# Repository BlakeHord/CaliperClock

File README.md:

# Caliper Clock

A low-power digital clock that uses the LCD salvaged from a cheap digital
caliper. The custom board drops into the caliper body, drives its 4-mux glass
directly, and is designed to operate for >1 year off a single 1.5V LR44 button cell.

Three major hardware revisions live in this repo.

## Revisions

| Dir | Board | Status |
|-----|-------|--------|
| [`Caliper_Clock_V1/`](Caliper_Clock_V1/) | ATtiny1616 + HT1621B LCD driver + RV-3028 RTC (incl. a test board) | original design |
| [`Caliper_Clock_V2/`](Caliper_Clock_V2/) | revised V1-class board **+ the working V2 firmware** | source of truth for the caliper LCD segment map & set-time UX. Battery depleted in days due to constant boost switching (wrong component choice) |
| [`Caliper_Clock_V3/`](Caliper_Clock_V3/) | **active redesign** around an **MSP430FR4133** (FRAM, integrated LCD_E + RTC, no HT1621) | hardware-verified, firmware **v1.0** running on the custom board |

**Active work is V3.** Its firmware ports the V2 segment map and time-setting
state machine onto the MSP430, displaying time on the real caliper glass via the
chip's built-in LCD controller and keeping time with the integrated RTC.

## V3 at a glance

- **MCU:** MSP430FR4133 (LCD_E drives the 4-mux caliper glass directly).
- **Power:** boosts a 1.5 V LR44 cell to 3.0 V (TPS61099); sleeps in LPM3 with
  the always-on LCD, targeting ~µA average for >year battery life.
- **Firmware:** `Caliper_Clock_V3/firmware/` — MSP430-GCC + `mspdebug`. The
  default build is the v1.0 product (full clock + buttons on the caliper glass);
  numbered diagnostic builds remain for bring-up. See its
  [README](Caliper_Clock_V3/firmware/README.md).
- **Hardware:** KiCad design, datasheets, and gerbers under `Caliper_Clock_V3/`.

```sh
cd Caliper_Clock_V3/firmware
make            # build v1.0 (the product)
make flash      # build + flash via the LaunchPad's eZ-FET (Spy-Bi-Wire)
```

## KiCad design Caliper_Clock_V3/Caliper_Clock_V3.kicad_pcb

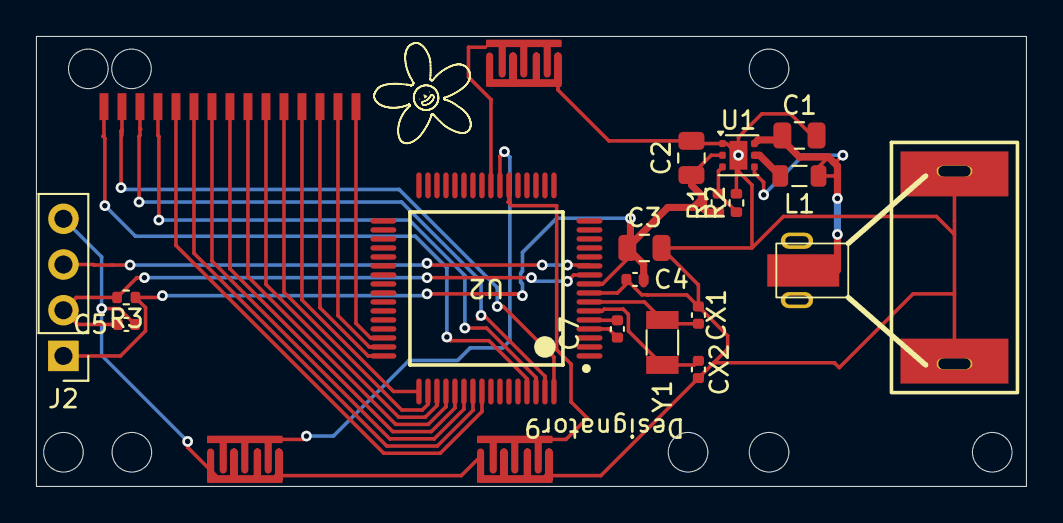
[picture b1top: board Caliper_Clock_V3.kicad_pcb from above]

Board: 2 copper layers, 55.0 x 25.0 mm, 22 parts (0 on the bottom side), 29 nets.

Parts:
C1, C2, C3: 10uF; C_0805_2012Metric
C4, C7: 100nF; C_0402_1005Metric
C5: 1nF; C_0402_1005Metric
CL_1: MY-ZJ-117
CL_2: MY-ZJ-118
CX1, CX2: 12pF; C_0402_1005Metric
J1: LCD PADS
J2: SBW; PinHeader_1x04_P2.54mm_Vertical
L1: 2.2uH; L_0805_2012Metric
R1: 2.0M; R_0402_1005Metric
R2: 1.0M; R_0402_1005Metric
R3: 47k; R_0402_1005Metric
SW1: MODE; Button_trace_caliper_board
SW2: HOUR; Button_trace_caliper_board
SW3: MIN; Button_trace_caliper_board
U1: TPS61099DRVR; WSON-6-1EP_2x2mm_P0.65mm_EP1x1.6mm
U2: MSP430FR4133IPM; PM0064A_N
Y1: 32.768kHz; Crystal_SMD_3215-2Pin_3.2x1.5mm

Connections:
+3V0: C2.1, C3.1, C4.1, J2.1, R1.1, R3.1, U1.2 (VOUT), U2.9 (DVCC)
+BATT: C1.1, L1.1, U1.4 (EN), U1.6 (VIN)
/BTN_HOUR: SW2.1, U2.23 (P1.1_UCA0RXD_UCA0SOMI_A1_Veref+)
/BTN_MIN: SW3.1, U2.22 (P1.2_UCA0CLK_A2)
/BTN_MODE: SW1.1, U2.24 (P1.0_UCA0TXD_UCA0SIMO_A0_Veref-)
/LCD_COM0: J1.2, U2.64 (P7.0_L0)
/LCD_COM1: J1.3, U2.63 (P7.1_L1)
/LCD_COM2: J1.4, U2.62 (P7.2_L2)
/LCD_COM3: J1.1, U2.61 (P7.3_L3)
/LCD_SEG0: J1.5, U2.56 (P3.0_L8)
/LCD_SEG1: J1.6, U2.55 (P3.1_L9)
/LCD_SEG2: J1.7, U2.54 (P3.2_L10)
/LCD_SEG3: J1.8, U2.53 (P3.3_L11)
/LCD_SEG4: J1.9, U2.52 (P3.4_L12)
/LCD_SEG5: J1.10, U2.51 (P3.5_L13)
/LCD_SEG6: J1.11, U2.50 (P3.6_L14)
/LCD_SEG7: J1.12, U2.49 (P3.7_L15)
/LCD_SEG8: J1.13, U2.48 (P6.0_L16)
/LCD_SEG9: J1.14, U2.47 (P6.1_L17)
/LCD_SEG10: J1.15, U2.46 (P6.2_L18)
/RST_n: C5.1, J2.2, R3.2, U2.10 (RST_NMI_SBWTDIO_N)
/TEST_SBWTCK: J2.3, U2.11 (TEST_SBWTCK)
/XIN: CX1.1, U2.7 (P4.1_XIN), Y1.1
/XOUT: CX2.1, U2.6 (P4.2_XOUT), Y1.2
GND: C1.2, C2.2, C3.2, C4.2, C5.2, CX1.2, CX2.2, J2.4, R2.2, SW1.2, SW2.2, SW3.2, U1.1 (GND), U1.7 (PAD/GND), U2.8 (DVSS)
unnamed: R1.2, R2.1, U1.3 (FB)
unnamed: L1.2, U1.5 (SW)
unnamed: C7.2, U2.5 (P4.3_LCDCAP0)
unnamed: C7.1, U2.4 (P4.4_LCDCAP1)

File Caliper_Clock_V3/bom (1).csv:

Comment,Designator,Footprint,LCSC Part #
"10uF","C1,C2,C3","C_0805_2012Metric","C15850"
"100nF","C4,C7","C_0402_1005Metric","C1525"
"1nF","C5","C_0402_1005Metric","C1523"
"12pF","CX1,CX2","C_0402_1005Metric","C1547"
"2.0M","R1","R_0402_1005Metric","C11512"
"1.0M","R2","R_0402_1005Metric","C26083"
"47k","R3","R_0402_1005Metric","C25792"
"2.2uH","L1","L_0805_2012Metric","C41651"
"32.768kHz","Y1","Crystal_SMD_3215-2Pin_3.2x1.5mm","C32346"
"TPS61099DRVR","U1","WSON-6-1EP_2x2mm_P0.65mm_EP1x1.6mm","C2842395"
"MSP430FR4133IPM","U2","PM0064A_N","C106759"
"MY-ZJ-117","CL_1","MY-ZJ-117","C964865"
"MY-FJ-118","CL_2","MY-FJ-118","C964866"

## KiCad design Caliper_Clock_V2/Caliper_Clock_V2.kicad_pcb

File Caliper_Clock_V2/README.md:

# Caliper Clock

A low-power digital clock built using a salvaged LCD display from a digital caliper, driven by an ATtiny1616 microcontroller with an RV-3028 real-time clock.

## Features

- **Ultra-low power consumption** — ATtiny1616 sleeps in power-down mode, waking only on RTC minute interrupts
- **12-hour time display** with AM/PM indicator and blinking colon
- **Button-based time setting** — long-press to enter setting mode, adjust hours/minutes with dedicated buttons
- **Accurate timekeeping** — RV-3028 RTC with minute-update interrupt
- **Repurposed LCD** — uses an HT1621B-compatible LCD from a digital caliper (4-digit 7-segment display)

## Hardware

### Components

| Component | Description |
|-----------|-------------|
| ATtiny1616 | 8-bit AVR microcontroller, 20 MHz, 20 pins, supports sleep modes, GPIO, interrupts |
| HT1621B | 32-nibble LCD driver, 4-com 1/3-bias, SPI/parallel interface |
| RV-3028 | I2C RTC, 24-hour mode, minute alarm output, ultra-low-power |
| AP3015AKTR-G1 | Boost Switching Regulator IC |

### Pin Mapping

#### LCD (HT1621B)
| Signal | Pin |
|--------|-----|
| DATA   | PA1 |
| WR     | PA7 |
| /CS    | PB3 |

#### RTC (RV-3028 via Soft I²C)
| Signal | Pin |
|--------|-----|
| SDA    | PA2 |
| SCL    | PA3 |
| INT    | PA4 |

#### Buttons
| Function | Pin |
|----------|-----|
| Mode     | PB0 |
| Hour+    | PB1 |
| Minute+  | PB2 |

#### Debug
| Function | Pin |
|----------|-----|
| LED      | PA6 |

## PCB Designs

The repository is organized into one folder per board revision:

- **Caliper_Clock_V1/** — Original board (includes the `Caliper_Clock_Test_Board/` test/development board)
- **Caliper_Clock_V2/** — Revised board design (also contains this firmware and tooling)
- **Caliper_Clock_V3/** — MSP430FR4133-based redesign (includes the `MSP430FR4133IPM/` symbol library)

Each folder contains:
- KiCad schematic (`.kicad_sch`)
- KiCad PCB layout (`.kicad_pcb`)
- Gerber files for manufacturing
- BOM and pick-and-place files

## Building the Firmware

### Prerequisites

- AVR-GCC toolchain (avr-gcc 14 recommended)
- avr-objcopy

On macOS with Homebrew:
```bash
brew install avr-gcc@14
```

### Compile

```bash
make clean
make
```

This produces `blink.hex` ready for flashing.

### Flash

Use a UPDI programmer (e.g., SerialUPDI, Atmel-ICE, or jtag2updi):

```bash
# Example with pymcuprog
pymcuprog write -t uart -u /dev/tty.usbserial-XXXX -d attiny1616 -f blink.hex
```

## Usage

### Normal Operation

- The clock displays time in 12-hour format with AM/PM indicator
- Colon blinks at ~1 Hz
- MCU sleeps between updates for minimal power consumption

### Setting the Time

1. **Long-press the Mode button (PB0)** for ~5 seconds to enter time-setting mode
2. Display will flash to indicate setting mode
3. **Press Hour button (PB1)** to increment hours (1-12)
4. **Press Minute button (PB2)** to increment minutes (0-59)
5. **Press Mode button (PB0)** again to save and exit

Hold Hour or Minute buttons for auto-repeat.

## Firmware Variants

The repository includes several firmware versions:

| File | Description |
|------|-------------|
| `main.c` | Current version with low-power mode and button time-setting |
| `main-CLOCK-V1.c` | Earlier clock implementation |
| `main-BASIC-CLOCK.c` | Basic clock without power optimization |
| `main-RTC-test.c` | RTC testing/debugging |
| `main-lcd_count.c` | LCD counting test |
| `main-lcd_walk.c` | LCD segment walking test |
| `main-blink_WR_CS_LED.c` | GPIO/LED blink test |

## Python Utilities

- **lcd_driver.py** — ESP32 MicroPython LCD driver (for prototyping)
- **lcd_screen_decoding.py** — LCD segment mapping analysis tool

## License

MIT License — feel free to use, modify, and share!

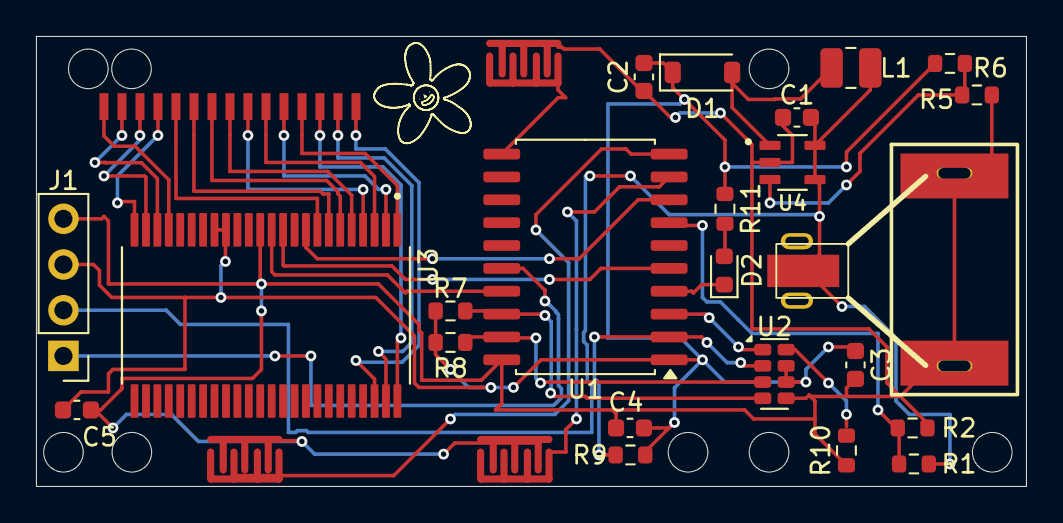
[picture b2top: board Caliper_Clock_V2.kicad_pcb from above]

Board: 2 copper layers, 55.0 x 25.0 mm, 42 parts (0 on the bottom side), 32 nets.

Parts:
C1: 10uF; C_0603_1608Metric
C2: 22uF; C_0603_1608Metric
C3, C4, C5: 0.1uF; C_0603_1608Metric
CL_1: MY-ZJ-117
CL_2: MY-ZJ-118
D1: MBR0540; D_SOD-123
D2: LED; D_0603_1608Metric
J1: Conn_01x04; PinHeader_1x04_P2.54mm_Vertical
L1: 10uH; L_1008_2520Metric
R1: 2.2M; R_0603_1608Metric
R2: 1.0M; R_0603_1608Metric
R5: 1.43M; R_0603_1608Metric
R6: 1.00M; R_0603_1608Metric
R7, R8: 10k; R_0603_1608Metric
R9: 47k; R_0603_1608Metric
R10: 100k; R_0603_1608Metric
R11: 1.1k; R_0603_1608Metric
TP1: PAD1; TestPoint_Pad_0.5mm_x_5.0mm
TP2: PAD2; TestPoint_Pad_0.5mm_x_5.0mm
TP3: PAD3; TestPoint_Pad_0.5mm_x_5.0mm
TP4: PAD4; TestPoint_Pad_0.5mm_x_5.0mm
TP5: PAD5; TestPoint_Pad_0.5mm_x_5.0mm
TP6: PAD6; TestPoint_Pad_0.5mm_x_5.0mm
TP7: PAD7; TestPoint_Pad_0.5mm_x_5.0mm
TP8: PAD8; TestPoint_Pad_0.5mm_x_5.0mm
TP9: PAD9; TestPoint_Pad_0.5mm_x_5.0mm
TP10: PAD10; TestPoint_Pad_0.5mm_x_5.0mm
TP11: PAD11; TestPoint_Pad_0.5mm_x_5.0mm
TP12: PAD12; TestPoint_Pad_0.5mm_x_5.0mm
TP13: PAD13; TestPoint_Pad_0.5mm_x_5.0mm
TP14: PAD14; TestPoint_Pad_0.5mm_x_5.0mm
TP15: PAD15; TestPoint_Pad_0.5mm_x_5.0mm
TP17: BTN2; Button_trace_caliper_board
TP18: BTN3; Button_trace_caliper_board
TP19: BTN4; Button_trace_caliper_board
U1: ATtiny1616-S; SOIC-20W_7.5x12.8mm_P1.27mm
U2: RV-3028-C7; MicroCrystal_C7_SON-8_1.5x3.2mm_P0.9mm
U3: HT1621B; SOP63P1035X279-48N
U4: AP3015AKTR-G1; SOT95P280X145-5N

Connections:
+1V5: C1.1, CL_1.3, J1.2, L1.2, R1.2, U4.4 (~SHDN), U4.5 (VIN)
+3V0: C2.2, C3.1, C4.2, C5.1, D1.1 (K), J1.3, R5.2, R7.2, R8.2, R9.2, R11.1, U1.1 (VCC), U2.6 (VBACKUP), U2.7 (VDD), U3.16 (VLCD), U3.17 (VDD)
/BAT_SENSE: R1.1, R2.2, U1.7 (PB4)
/CLKOUT: U1.3 (PA5), U2.1 (CLKOUT)
/COM0: TP1.1, U3.21 (COM0)
/COM1: TP2.1, U3.22 (COM1)
/COM2: TP3.1, U3.23 (COM2)
/COM3: TP4.1, U3.24 (COM3)
/INT: R9.1, U1.2 (PA4), U2.2 (~INT)
/LCD_CS: U1.8 (PB3), U3.9 (~CS)
/LCD_DATA: U1.17 (PA1), U3.12 (DATA)
/LCD_WR: U1.5 (PA7), U3.11 (~WR)
/SCL: R8.1, U1.19 (PA3), U2.3 (SCL)
/SDA: R7.1, U1.18 (PA2), U2.4 (SDA)
/UPDI: J1.1, U1.16 (~RESET/PA0)
GND: C1.2, C2.1, C3.2, C4.1, C5.2, CL_2.1, CL_2.2, J1.4, R2.1, R6.2, R10.1, U1.9 (PB2), U1.10 (PB1), U1.11 (PB0), U1.20 (GND), U2.5 (VSS), U3.13 (VSS), U4.2 (GND)
unnamed: D1.2 (A), L1.1, U4.1 (SW)
unnamed: D2.2 (A), R11.2
unnamed: D2.1 (K), U1.4 (PA6)
unnamed: R10.2, U2.8 (EVI)
unnamed: TP5.1, U3.8 (SEG0)
unnamed: TP6.1, U3.7 (SEG1)
unnamed: TP7.1, U3.6 (SEG2)
unnamed: TP8.1, U3.5 (SEG3)
unnamed: TP9.1, U3.4 (SEG4)
unnamed: TP10.1, U3.3 (SEG5)
unnamed: TP11.1, U3.2 (SEG6)
unnamed: TP12.1, U3.1 (SEG7)
unnamed: TP13.1, U3.48 (SEG8)
unnamed: TP14.1, U3.47 (SEG9)
unnamed: TP15.1, U3.46 (SEG10)
unnamed: R5.1, R6.1, U4.3 (FB)

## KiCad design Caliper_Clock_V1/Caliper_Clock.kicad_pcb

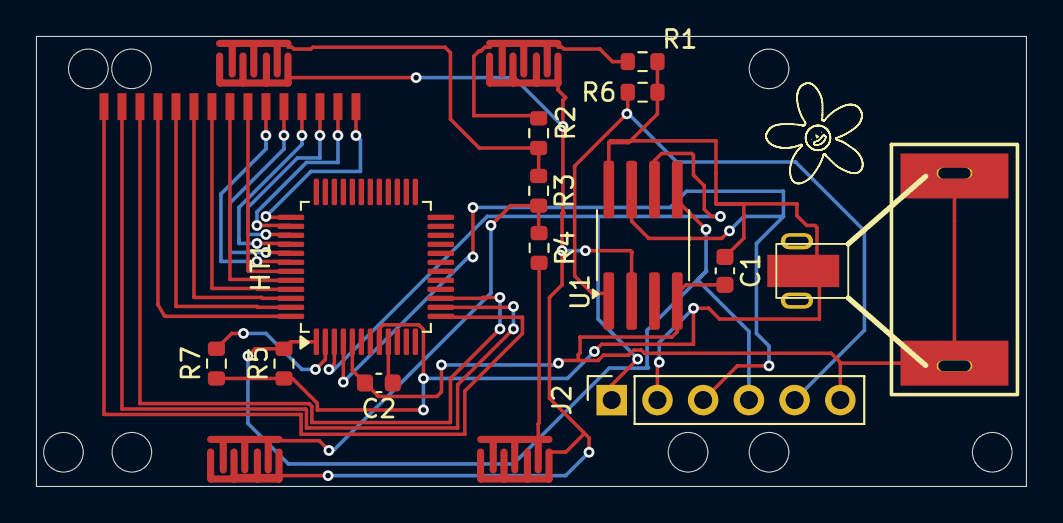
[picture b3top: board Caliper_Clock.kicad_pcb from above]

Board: 2 copper layers, 55.0 x 25.0 mm, 33 parts (0 on the bottom side), 24 nets.

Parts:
C1, C2: C100n; C_0603_1608Metric
CL_1: MY-ZJ-117
CL_2: MY-ZJ-118
HT1: LQFP-48_7x7mm_P0.5mm
J2: Conn_01x06; PinSocket_1x06_P2.54mm_Vertical
R1, R6: R10k; R_0603_1608Metric
R2: R20k; R_0603_1608Metric
R3: R30k; R_0603_1608Metric
R4: R40k; R_0603_1608Metric
R5, R7: R4.7k; R_0603_1608Metric
TP1: PAD1; TestPoint_Pad_0.5mm_x_5.0mm
TP2: PAD2; TestPoint_Pad_0.5mm_x_5.0mm
TP3: PAD3; TestPoint_Pad_0.5mm_x_5.0mm
TP4: PAD4; TestPoint_Pad_0.5mm_x_5.0mm
TP5: PAD5; TestPoint_Pad_0.5mm_x_5.0mm
TP6: PAD6; TestPoint_Pad_0.5mm_x_5.0mm
TP7: PAD7; TestPoint_Pad_0.5mm_x_5.0mm
TP8: PAD8; TestPoint_Pad_0.5mm_x_5.0mm
TP9: PAD9; TestPoint_Pad_0.5mm_x_5.0mm
TP10: PAD10; TestPoint_Pad_0.5mm_x_5.0mm
TP11: PAD11; TestPoint_Pad_0.5mm_x_5.0mm
TP12: PAD12; TestPoint_Pad_0.5mm_x_5.0mm
TP13: PAD13; TestPoint_Pad_0.5mm_x_5.0mm
TP14: PAD14; TestPoint_Pad_0.5mm_x_5.0mm
TP15: PAD15; TestPoint_Pad_0.5mm_x_5.0mm
TP16: BTN1; Button_trace_caliper_board
TP17: BTN2; Button_trace_caliper_board
TP18: BTN3; Button_trace_caliper_board
TP19: BTN4; Button_trace_caliper_board
U1: ATtiny85-20M; SOIC-8_3.9x4.9mm_P1.27mm

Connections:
GND: C1.2, C2.2, HT1.5 (VSS), J2.6, U1.4 (GND)
unnamed: HT1.13 (COM0), TP1.1
unnamed: HT1.14 (COM1), TP2.1
unnamed: HT1.15 (COM2), TP3.1
unnamed: HT1.1 (CS), J2.4, R5.2, U1.5 (AREF/PB0)
unnamed: HT1.4 (DATA), J2.3, U1.7 (PB2)
unnamed: HT1.2 (RD), R7.2
unnamed: HT1.48 (SEG0), TP4.1
unnamed: HT1.47 (SEG1), TP5.1
unnamed: HT1.46 (SEG2), TP6.1
unnamed: HT1.45 (SEG3), TP7.1
unnamed: HT1.44 (SEG4), TP8.1
unnamed: HT1.43 (SEG5), TP9.1
unnamed: HT1.42 (SEG6), TP10.1
unnamed: HT1.41 (SEG7), TP11.1
unnamed: HT1.40 (SEG8), TP12.1
unnamed: HT1.39 (SEG9), TP13.1
unnamed: HT1.38 (SEG10), TP14.1
unnamed: HT1.37 (SEG11), TP15.1
unnamed: C2.1, HT1.9 (VDD)
unnamed: HT1.3 (WR), J2.1, U1.6 (PB1)
unnamed: J2.5, R6.2, U1.1 (~RESET/PB5)
unnamed: R1.2, R2.1, R2.2, R3.1, R3.2, R4.1, R4.2, U1.2 (XTAL1/PB3)
VCC: C1.1, HT1.8 (VLCD), J2.2, R1.1, R5.1, R6.1, R7.1, U1.8 (VCC)

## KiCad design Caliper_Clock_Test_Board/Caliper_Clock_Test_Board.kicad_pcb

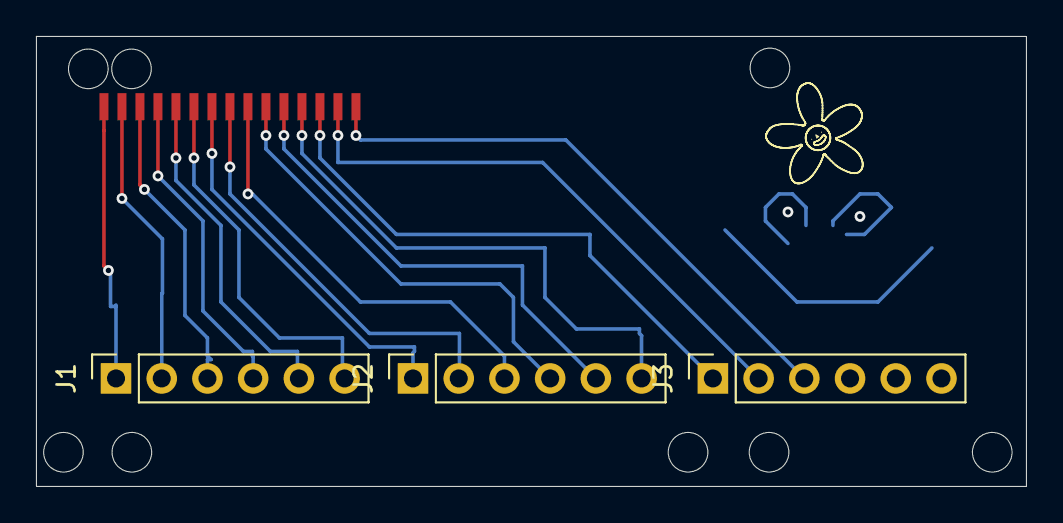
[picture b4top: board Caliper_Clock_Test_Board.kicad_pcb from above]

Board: 2 copper layers, 55.0 x 25.0 mm, 18 parts (0 on the bottom side), 15 nets.

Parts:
J1, J2, J3: Conn_01x06; PinSocket_1x06_P2.54mm_Vertical
TP1: PAD1; TestPoint_Pad_0.5mm_x_5.0mm
TP2: PAD2; TestPoint_Pad_0.5mm_x_5.0mm
TP3: PAD3; TestPoint_Pad_0.5mm_x_5.0mm
TP4: PAD4; TestPoint_Pad_0.5mm_x_5.0mm
TP5: PAD5; TestPoint_Pad_0.5mm_x_5.0mm
TP6: PAD6; TestPoint_Pad_0.5mm_x_5.0mm
TP7: PAD7; TestPoint_Pad_0.5mm_x_5.0mm
TP8: PAD8; TestPoint_Pad_0.5mm_x_5.0mm
TP9: PAD9; TestPoint_Pad_0.5mm_x_5.0mm
TP10: PAD10; TestPoint_Pad_0.5mm_x_5.0mm
TP11: PAD11; TestPoint_Pad_0.5mm_x_5.0mm
TP12: PAD12; TestPoint_Pad_0.5mm_x_5.0mm
TP13: PAD13; TestPoint_Pad_0.5mm_x_5.0mm
TP14: PAD14; TestPoint_Pad_0.5mm_x_5.0mm
TP15: PAD15; TestPoint_Pad_0.5mm_x_5.0mm

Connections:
unnamed: J1.1, TP1.1
unnamed: J1.2, TP2.1
unnamed: J1.3, TP3.1
unnamed: J1.4, TP4.1
unnamed: J1.5, TP5.1
unnamed: J1.6, TP6.1
unnamed: J2.1, TP7.1
unnamed: J2.2, TP8.1
unnamed: J2.3, TP9.1
unnamed: J2.4, TP10.1
unnamed: J2.5, TP11.1
unnamed: J2.6, TP12.1
unnamed: J3.1, TP13.1
unnamed: J3.2, TP14.1
unnamed: J3.3, TP15.1

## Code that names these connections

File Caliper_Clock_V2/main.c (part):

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// Behavior:
//   - RV-3028 runs in 24h mode, keeps real time.
//   - Minute interrupt wakes ATtiny from sleep.
//   - PB0 long-press enters time-setting mode.
//   - PB1/PB2 increment hour/minute while in time-setting mode.
// -----------------------------------------------------------------------------

#define F_CPU 3333333UL
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// PIN MAP (LCD / LED)
// -----------------------------------------------------------------------------
#define HT_DATA_PORT   PORTA
#define HT_DATA_PIN    1       // PA1

#define HT_WR_PORT     PORTA
#define HT_WR_PIN      7       // PA7

#define HT_CS_PORT     PORTB
#define HT_CS_PIN      3       // PB3 (/CS active-low)

#define LED_PORT       PORTA
#define LED_PIN        6       // PA6 (optional debug LED)

#define HT_N_ADDR      32      // 32 nibbles

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// PIN MAP (soft I2C for RV-3028 and INT)
// -----------------------------------------------------------------------------
#define SDA_PORT   PORTA
#define SDA_PIN    2   // PA2
#define SCL_PORT   PORTA
#define SCL_PIN    3   // PA3

// RTC INT -> PA4
#define RTC_INT_PORT    PORTA
#define RTC_INT_PIN     4      // PA4

// -----------------------------------------------------------------------------
// BUTTONS
// -----------------------------------------------------------------------------
#define BTN_MODE_PORT   PORTB
#define BTN_MODE_PIN    0   // PB0, enter time-setting mode

#define BTN_HOUR_PORT   PORTB
#define BTN_HOUR_PIN    1   // PB1, increment hour

#define BTN_MIN_PORT    PORTB
#define BTN_MIN_PIN     2   // PB2, increment minute

#define BTN_DEBOUNCE_MS 20   // 20 ms debounce

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// -----------------------------------------------------------------------------
volatile uint8_t colon_on = 0;                // toggled by PIT ~1 Hz
volatile uint8_t needs_display_refresh = 0;   // set by PIT and/or RTC INT
volatile uint8_t minute_tick_flag = 0;        // set by RTC INT (PA4 ISR)

// Current displayed time (12-hour + PM)
volatile uint8_t cur_hour12 = 12;
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}

// -----------------------------------------------------------------------------
// RTC PIT (~1 Hz) & INT PA4 Setup
// -----------------------------------------------------------------------------
static void rtc_pit_init_1Hz(void){
    RTC.CTRLA=RTC_RTCEN_bm;
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}

// -----------------------------------------------------------------------------
// Time-Setting Mode (PB0 long-press enters this)
// -----------------------------------------------------------------------------
// -----------------------------------------------------------------------------
// Time-Setting Mode (PB0 long-press enters this)
// Flash digits briefly while keeping colon/PM blinking
// -----------------------------------------------------------------------------
static void time_setting_mode(void) {
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    uint16_t hour_hold_counter = 0;       // button hold counters
    uint16_t min_hold_counter  = 0;

    // Wait for PB0 release before starting
    while (!(BTN_MODE_PORT.IN & _BV8(BTN_MODE_PIN))) {
        _delay_ms(20);
    }

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            lcd_show_4digit(cur_hour12 * 100 + cur_min, colon_on, cur_pm);
        }

        // --- Hour button (PB1) with debounce + repeat) ---
        if (!(BTN_HOUR_PORT.IN & _BV8(BTN_HOUR_PIN))) {
            hour_hold_counter++;
            if (hour_hold_counter == 1 || hour_hold_counter >= 20) { 
                cur_hour12++;
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            hour_hold_counter = 0;
        }

        // --- Minute button (PB2) with debounce + repeat) ---
        if (!(BTN_MIN_PORT.IN & _BV8(BTN_MIN_PIN))) {
            min_hold_counter++;
            if (min_hold_counter == 1 || min_hold_counter >= 20) {
                cur_min++;
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            min_hold_counter = 0;
        }

        // --- Exit on PB0 new press ---
        if (!(BTN_MODE_PORT.IN & _BV8(BTN_MODE_PIN))) {
            _delay_ms(50); // debounce
            if (!(BTN_MODE_PORT.IN & _BV8(BTN_MODE_PIN))) break;
        }

        _delay_ms(20); // main loop interval
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    }

    // Buttons: pull-ups
    BTN_MODE_PORT.PIN0CTRL = PORT_PULLUPEN_bm;
    BTN_HOUR_PORT.PIN1CTRL = PORT_PULLUPEN_bm;
    BTN_MIN_PORT.PIN2CTRL = PORT_PULLUPEN_bm;
    BTN_MODE_PORT.DIRCLR=_BV8(BTN_MODE_PIN);
    BTN_HOUR_PORT.DIRCLR=_BV8(BTN_HOUR_PIN);
    BTN_MIN_PORT.DIRCLR=_BV8(BTN_MIN_PIN);

    sei();
    set_sleep_mode(SLEEP_MODE_PWR_DOWN);
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            lcd_show_4digit(cur_hour12*100+cur_min,colon_on,cur_pm);
        }

        // PB0 long press detection
        if(!(BTN_MODE_PORT.IN & _BV8(BTN_MODE_PIN))){
            uint16_t pressed_ms=0;
            while(!(BTN_MODE_PORT.IN & _BV8(BTN_MODE_PIN))){
                _delay_ms(10); pressed_ms+=10;
                if(pressed_ms>=5000){ time_setting_mode(); break; }
            }
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
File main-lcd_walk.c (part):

// CaliperClock bring-up: ATtiny1616 + HT1621B
// Mode: "ALL SEGMENTS ON" (continuous burst refresh) + LED heartbeat
// Pins (confirmed):
//   DATA = PA1, WR = PA7, /CS = PB3, LED(sink) = PA6
// Toolchain: avr-gcc; Program via pyupdi

#define F_CPU 3333333UL
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
// ---------- Pin mapping ----------
#define HT_DATA_PORT   PORTA
#define HT_DATA_PIN    1       // PA1
#define HT_WR_PORT     PORTA
#define HT_WR_PIN      7       // PA7
#define HT_CS_PORT     PORTB
#define HT_CS_PIN      3       // PB3 (/CS active-low)
#define LED_PORT       PORTA
#define LED_PIN        6       // PA6 (active-low LED sink)

// ---------- LCD geometry / timings ----------
#define HT_N_ADDR      32      // 32 nibbles (SEG addresses)
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
// ---------- One-at-a-time segment walker ----------
// Set how many COM bits to exercise and (optionally) shift which nibble bit is used.
// For normal 3-COM wiring on controller COM0..COM2: HT_COM_BITS=3, HT_COM_SHIFT=0
// For your "glass on controller COM1..COM3" case in 4-COM mode: HT_COM_BITS=3, HT_COM_SHIFT=1
#ifndef HT_COM_BITS
#define HT_COM_BITS   4
#endif
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
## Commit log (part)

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2025-09-08 Initial commit: ESP32 LCD driver and upload tools
    - Add lcd_driver.py: Clean ESP32 bare-glass LCD driver for CaliperClock
    - Add upload_to_esp32.sh: Enhanced upload script with progress indicator
    - Add README.md: Project documentation
2025-09-08 Remove lcd_screen_decoding.py from tracking
2026-01-05 Add complete Caliper Clock project files
    - KiCad PCB designs (V1, V2, Test Board)
    - Gerber files for manufacturing
    - ESP32 firmware source code (main.c and variants)
    - Python LCD driver and screen decoding utilities
    - Makefile for building
    - BOM and position files for assembly
2026-01-05 Add comprehensive README with project documentation
2026-01-05 remove some AI slop
2026-06-09 hw: fix boost inductor rail; re-route and regen fab outputs
    Fix the inductor (L1) wiring on the TPS61099 boost: it was tied to
    +3V0 (VOUT) instead of +BATT (VIN), so there was no inductor path from
    the cell into SW and the +3V0 rail stayed dead. Schematic now ties L1 to
    +BATT. This was the root cause of the dead / 0.1 V rail (bench-confirmed
    by jumpering L1 to +BATT, which brought +3V0 up to 3.0 V).
    Re-route the PCB for the corrected net and regenerate Gerbers2/ + BOM/CPL
2026-06-09 fw: make v1.0 product the default build; add READMEs
    Makefile: default to BRINGUP=7 (the v1.0 product — full clock on the
    caliper glass with buttons), add FW_VERSION and a build banner so the
    product vs. a diagnostic build is obvious. Numbered bring-up/diagnostic
    builds stay selectable via `make BRINGUP=N`.
    Docs: update the firmware README to reflect the default product build and
    the on-board verification status, and add a concise top-level repo README.
